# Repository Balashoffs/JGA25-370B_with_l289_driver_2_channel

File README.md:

# JGA25-370B_with_l289_driver_2_channel

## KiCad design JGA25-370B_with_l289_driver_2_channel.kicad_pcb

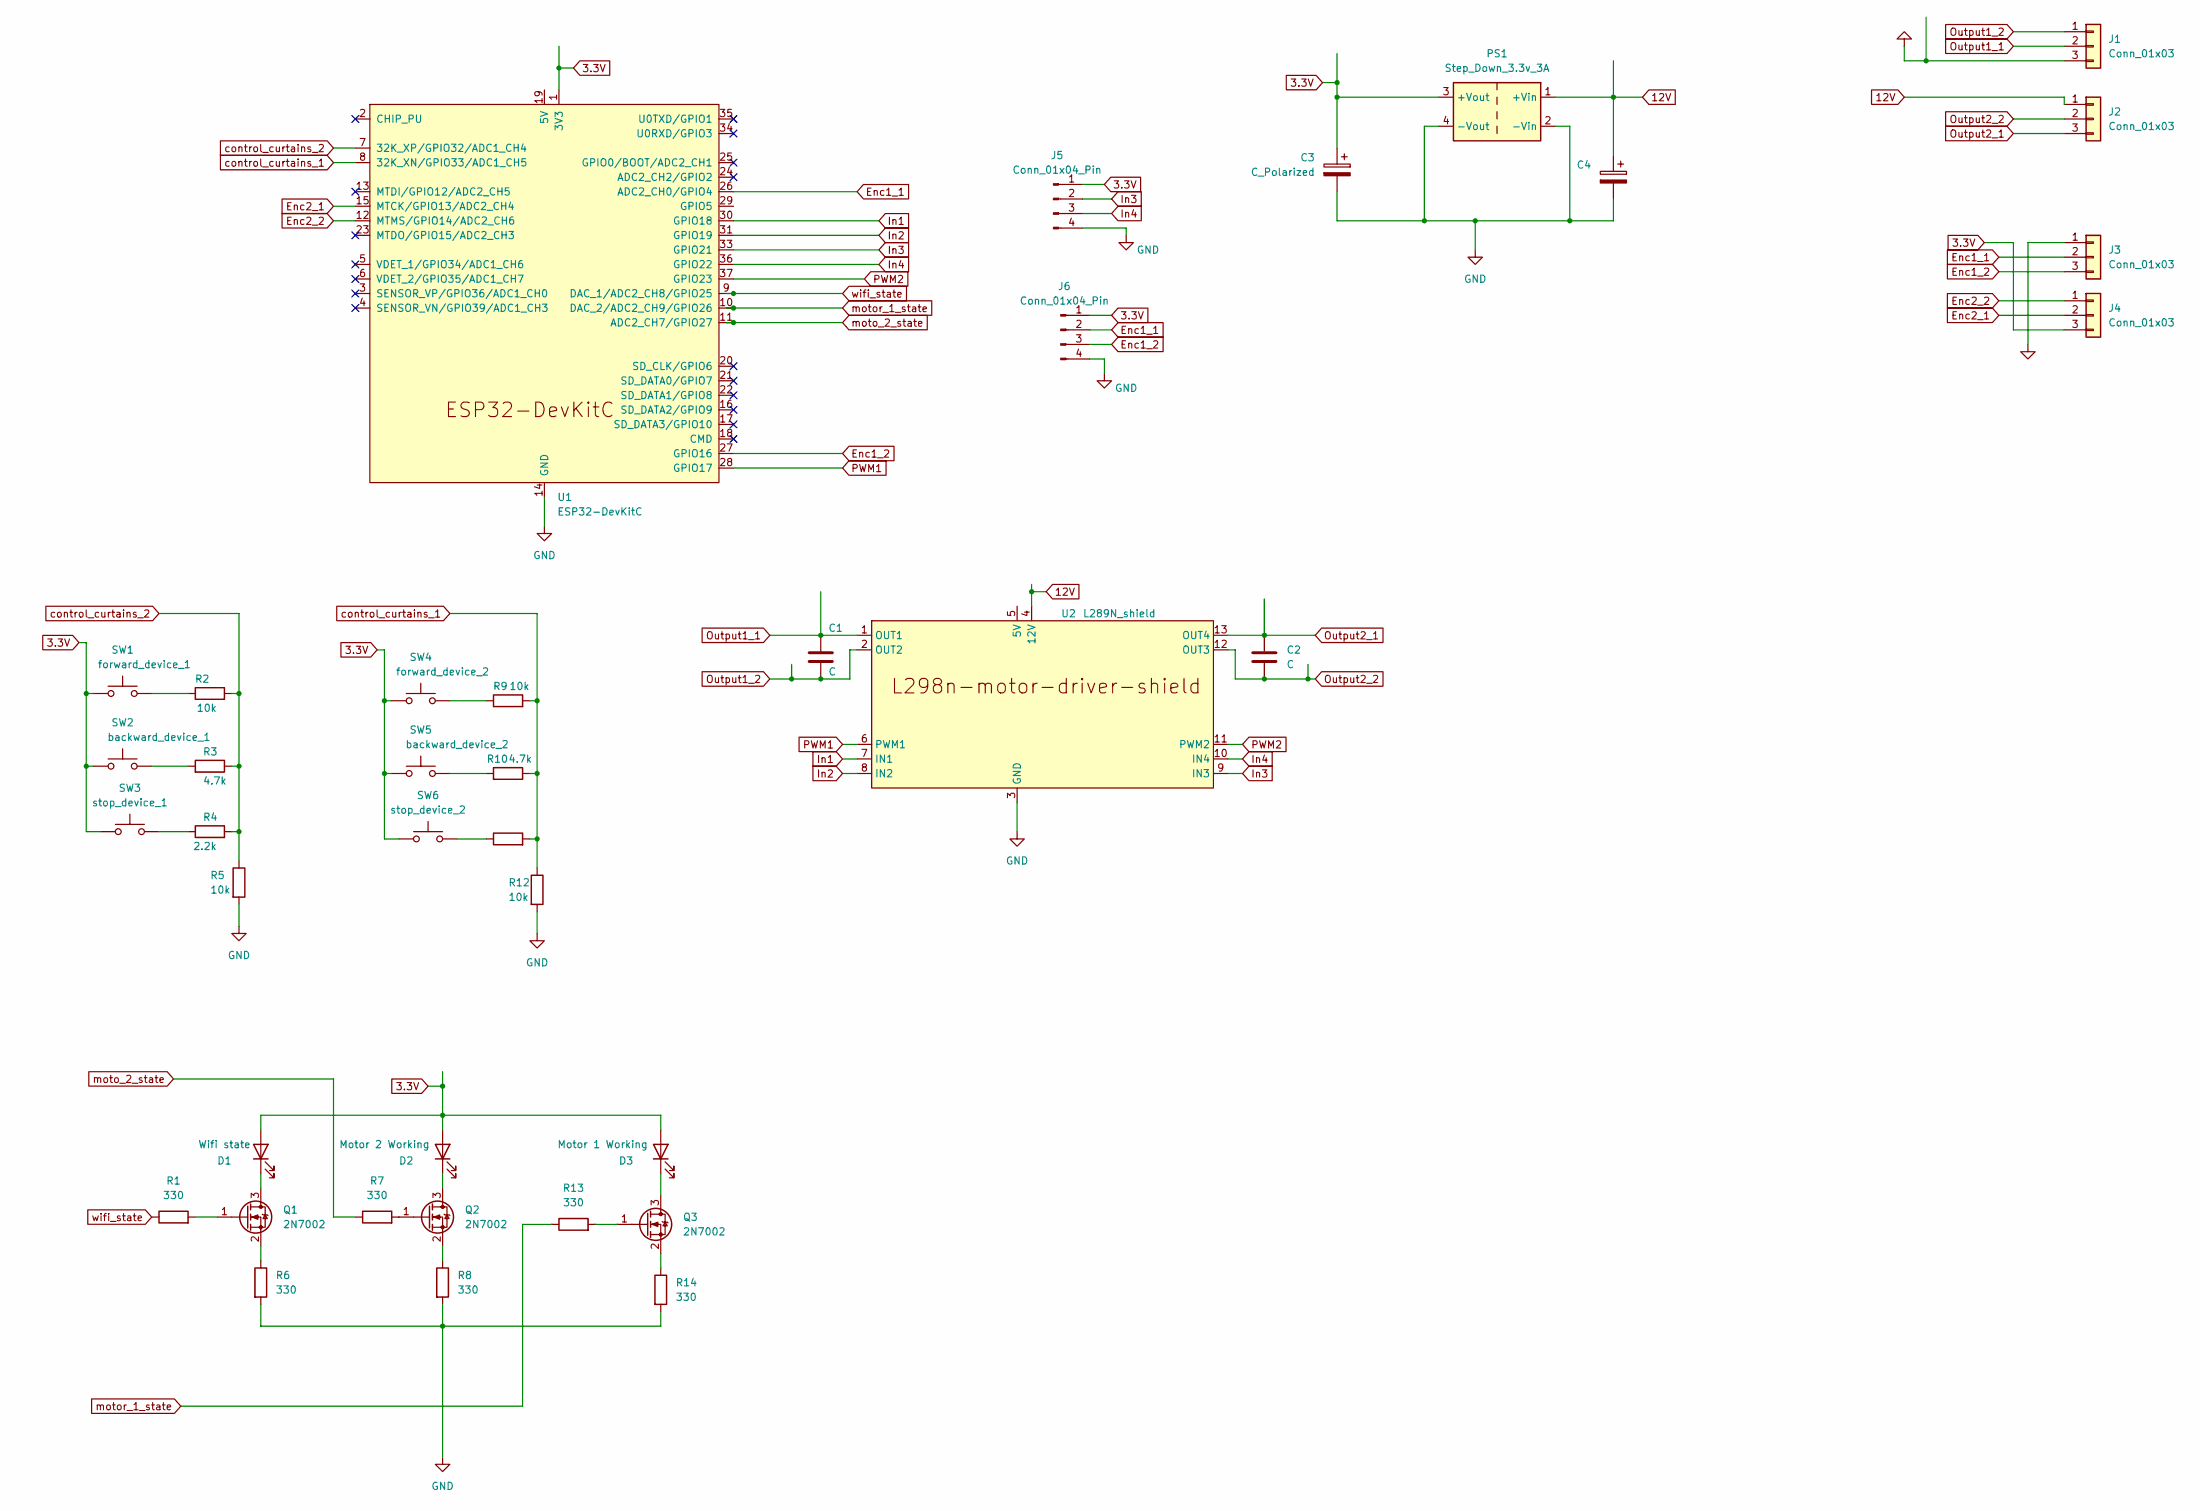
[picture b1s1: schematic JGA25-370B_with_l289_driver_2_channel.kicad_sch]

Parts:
C1, C2: C; C_Disc_D9.0mm_W5.0mm_P5.00mm
C3: C_Polarized; CP_Radial_D10.0mm_P2.50mm
C4: c=C_Polarized; CP_Radial_D10.0mm_P2.50mm
D1: Wifi state; LED_D3.0mm
D2: Motor 2 Working; LED_D3.0mm
D3: Motor 1 Working; LED_D3.0mm
J1, J2, J3, J4: Conn_01x03; TerminalBlock_MetzConnect_Type101_RT01603HBWC_1x03_P5.08mm_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
J5, J6: Conn_01x04_Pin; PinHeader_1x04_P2.54mm_Vertical
PS1: Step_Down_3.3v_3A; Converter_DCDC_3A_step_down_3.3v
Q1, Q2, Q3: 2N7002; SOT-23
R1, R6, R7, R8, R11, R13, R14: 330; R_1206_3216Metric
R2, R5, R9, R12: 10k; R_1206_3216Metric
R3, R10: 4.7k; R_1206_3216Metric
R4: 2.2k; R_1206_3216Metric
SW1: forward_device_1; SW_PUSH_6mm_H4.3mm
SW2: backward_device_1; SW_PUSH_6mm_H4.3mm
SW3: stop_device_1; SW_PUSH_6mm_H4.3mm
SW4: forward_device_2; SW_PUSH_6mm_H4.3mm
SW5: backward_device_2; SW_PUSH_6mm_H4.3mm
SW6: stop_device_2; SW_PUSH_6mm_H4.3mm
U1: ESP32-DevKitC
U2: L289N_shield; L298n_motor_driver_shield

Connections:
3.3V: C3.1, D1.2 (A), D2.2 (A), D3.2 (A), J4.3, J5.1, J6.1, PS1.3 (+Vout), SW1.1, SW2.1, SW3.1, SW4.1, SW5.1, SW6.1, U1.1 (3V3)
12V: C4.1, J2.1, PS1.1 (+Vin), U2.4 (12V)
Enc1_1: J3.2, J6.2, U1.26 (ADC2_CH0/GPIO4)
Enc1_2: J3.3, J6.3, U1.27 (GPIO16)
Enc2_1: J4.2, U1.15 (MTCK/GPIO13/ADC2_CH4)
Enc2_2: J4.1, U1.12 (MTMS/GPIO14/ADC2_CH6)
GND: C3.2, C4.2, J1.3, J3.1, J5.4, J6.4, PS1.2 (-Vin), PS1.4 (-Vout), R5.2, R6.2, R8.2, R12.2, R14.2, U1.14 (GND), U1.32 (GND), U1.38 (GND), U2.3 (GND)
In1: U1.30 (GPIO18), U2.7 (IN1)
In2: U1.31 (GPIO19), U2.8 (IN2)
In3: J5.2, U1.33 (GPIO21), U2.9 (IN3)
In4: J5.3, U1.36 (GPIO22), U2.10 (IN4)
unnamed: D1.1 (K), Q1.3 (D)
unnamed: D2.1 (K), Q2.3 (D)
unnamed: D3.1 (K), Q3.3 (D)
unnamed: Q1.1 (G), R1.2
unnamed: Q1.2 (S), R6.1
unnamed: Q2.1 (G), R7.2
unnamed: Q2.2 (S), R8.1
unnamed: Q3.1 (G), R13.2
unnamed: Q3.2 (S), R14.1
unnamed: R2.1, SW1.2
unnamed: R3.2, SW2.2
unnamed: R4.1, SW3.2
unnamed: R9.1, SW4.2
unnamed: R10.2, SW5.2
unnamed: R11.1, SW6.2
Output1_1: C1.1, J1.2, U2.1 (OUT1)
Output1_2: C1.2, J1.1, U2.2 (OUT2)
Output2_1: C2.1, J2.3, U2.13 (OUT4)
Output2_2: C2.2, J2.2, U2.12 (OUT3)
PWM1: U1.28 (GPIO17), U2.6 (PWM1)
PWM2: U1.37 (GPIO23), U2.11 (PWM2)
control_curtains_1: R9.2, R10.1, R11.2, R12.1, U1.8 (32K_XN/GPIO33/ADC1_CH5)
control_curtains_2: R2.2, R3.1, R4.2, R5.1, U1.7 (32K_XP/GPIO32/ADC1_CH4)
moto_2_state: R7.1, U1.11 (ADC2_CH7/GPIO27)
motor_1_state: R13.1, U1.10 (DAC_2/ADC2_CH9/GPIO26)
wifi_state: R1.1, U1.9 (DAC_1/ADC2_CH8/GPIO25)

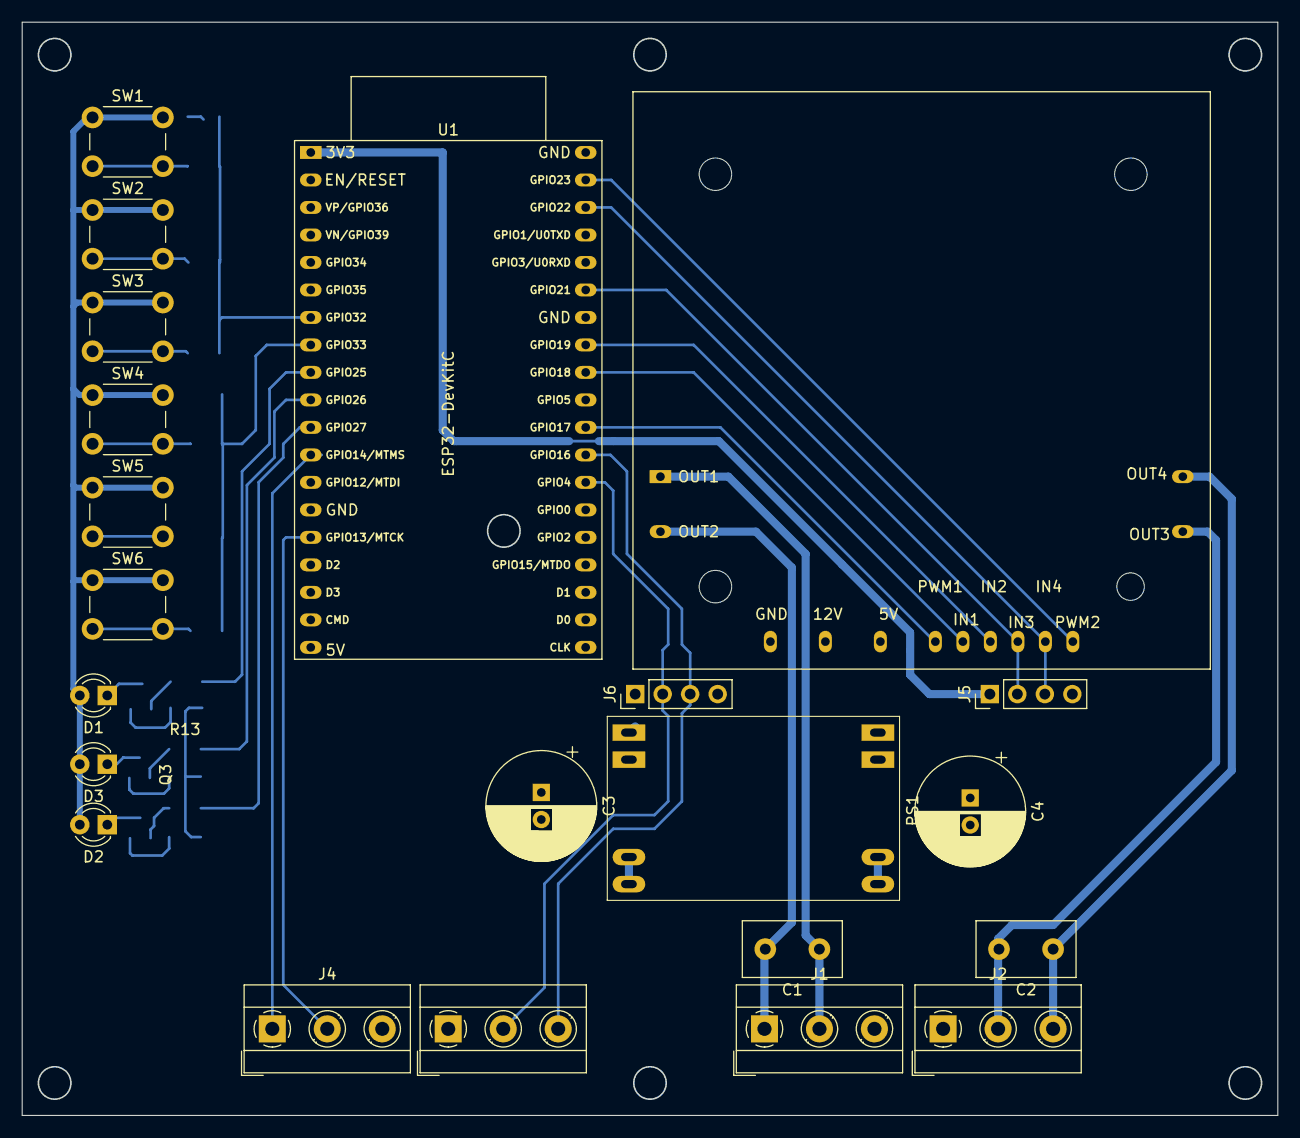
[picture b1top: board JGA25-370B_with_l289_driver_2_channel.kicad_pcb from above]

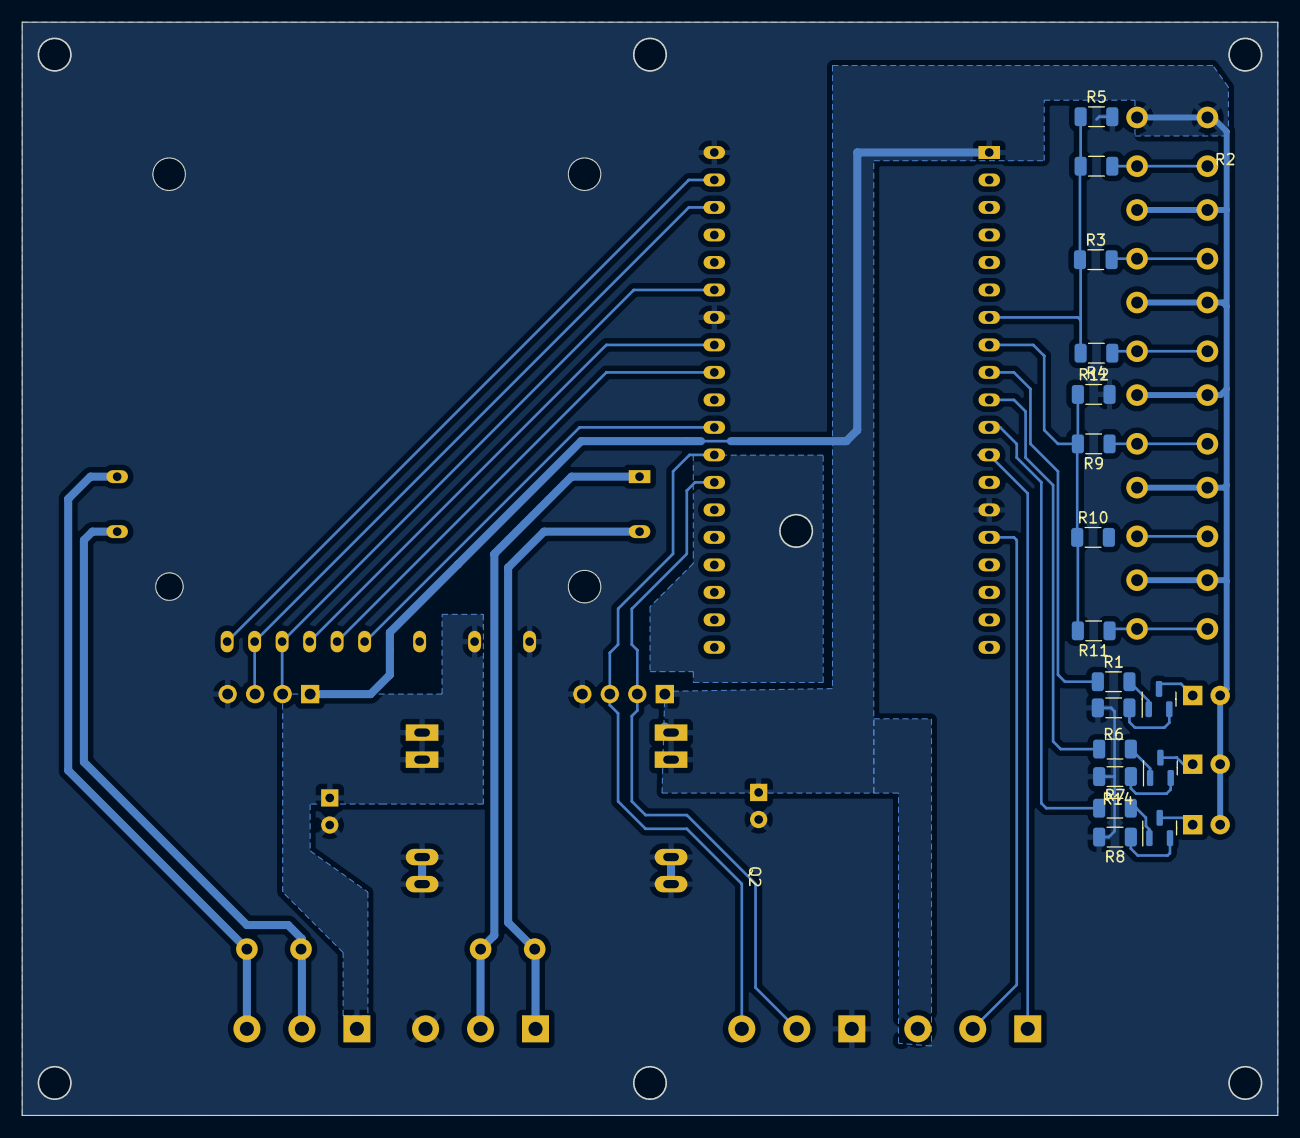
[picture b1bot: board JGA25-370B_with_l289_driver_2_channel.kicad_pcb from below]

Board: 2 copper layers, 116.0 x 100.9 mm, 39 parts (17 on the bottom side), 37 nets.

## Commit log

2024-07-08 add schematic
2024-07-17 fix nets
2024-08-19 ready for order
2024-08-19 add picture of schematic and 3d pcb board view
